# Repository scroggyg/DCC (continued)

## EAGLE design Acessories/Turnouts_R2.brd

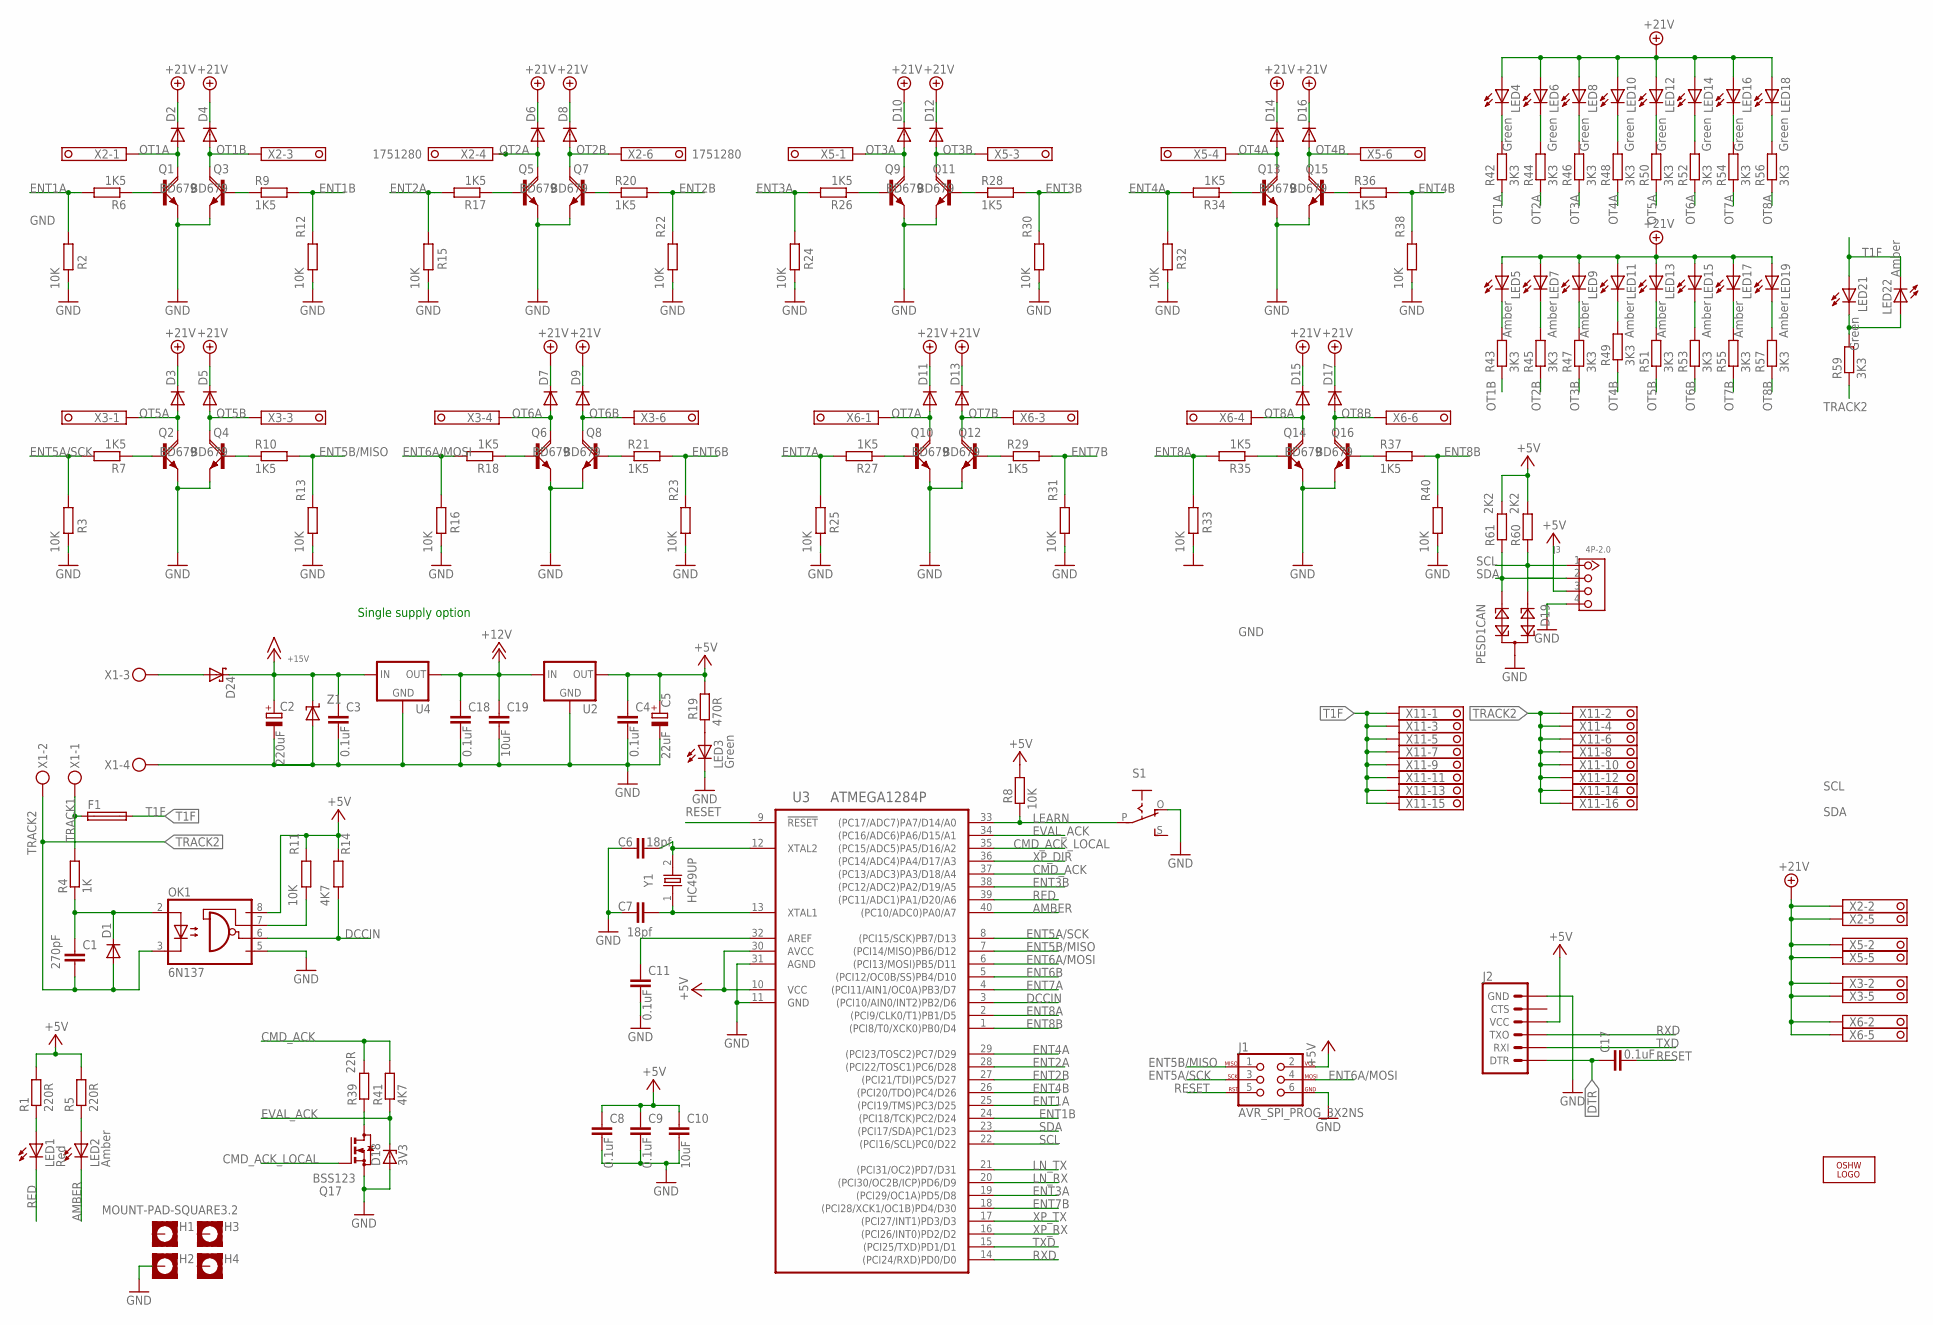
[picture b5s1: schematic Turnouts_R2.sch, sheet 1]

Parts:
C1: 270pF; C0805
C2: 220uF; E7,5-16
C3, C4, C8, C9, C11, C17, C18: 0.1uF; C0805
C5: 22uF; E2,5-5
C6, C7: 18pf; C0603
C10, C19: 10uF; C0805
D1, D2, D3, D4, D5, D6, D7, D8, D9, D10, D11, D12, D13, D14, D15, D16, D17: CGRM4002-G; SOD-123_MINI-SMA
D18: 3V3; SOT23
D19: PESD1CAN; SOT23
D24: MICROSMD-SCHOTTKY-DIODESMP; SMP
F1: TE5
H1, H2, H3, H4: MOUNT-PAD-SQUARE3.2; 3,2-PAD-SQUARE
J1: AVR_SPI_PROG_3X2NS; 2X3-NS
J2: 6_PIN_SERIAL_TARGET; 1X06
J3: 4P-2.0; HW4-2.0
LED1: Red; LED3MM
LED2, LED5, LED7, LED9, LED11, LED13, LED15, LED17, LED19, LED22: Amber; LED3MM
LED3, LED4, LED6, LED8, LED10, LED12, LED14, LED16, LED18, LED21: Green; LED3MM
LOGO1: OSHW_LOGO_6MILX0200-NT; OSHW_6X200_NOTEXT
OK1: 6N137; DIL08
Q1, Q2, Q3, Q4, Q5, Q6, Q7, Q8, Q9, Q10, Q11, Q12, Q13, Q14, Q15, Q16: BD679; TO126AV
Q17: BSS123; SOT23
R1, R5: 220R; R0805
R2, R3, R8, R11, R12, R13, R15, R16, R22, R23, R24, R25, R30, R31, R32, R33, R38, R40: 10K; R0805
R4: 1K; R0805
R6, R7, R9, R10, R17, R18, R20, R21, R26, R27, R28, R29, R34, R35, R36, R37: 1K5; R0805
R14, R41: 4K7; R0805
R19: 470R; R0805
R39: 22R; R0805
R42, R43, R44, R45, R46, R47, R48, R49, R50, R51, R52, R53, R54, R55, R56, R57, R59: 3K3; R0805
R60, R61: 2K2; R0805
S1: EG1218S; EG1218
U2, U4: V_REG_78XX-TO-220; TO-220-ALT
U3: ATMEGA1284P; DIP40
X1: MKDSN1,5/4-5,08
X2, X3, X5, X6: 1751280
X11: MKKDS1/8-3,5
Y1: HC49UP
Z1: TRANSZORB; SMB

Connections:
+5V: C4.1, C5.+, C8.1, C9.1, C10.1, J1.2, J2.4 (VCC), J3.3, OK1.8 (VCC), R1.2, R5.2, R8.2, R11.2, R14.2, R19.2, R60.2, R61.2, U2.OUT, U3.10 (VCC), U3.30 (AVCC); also elsewhere on the board
+12V: C18.1, C19.1, U2.IN, U4.OUT; also elsewhere on the board
+15V: C2.+, C3.1, D24.C, U4.IN, Z1.1 (C); also elsewhere on the board
+21V: D2.C, D3.C, D4.C, D5.C, D6.C, D7.C, D8.C, D9.C, D10.C, D11.C, D12.C, D13.C, D14.C, D15.C, D16.C, D17.C, LED4.A, LED5.A, LED6.A, LED7.A, LED8.A, LED9.A, LED10.A, LED11.A, LED12.A, LED13.A, LED14.A, LED15.A, LED16.A, LED17.A, LED18.A, LED19.A, X2.2, X2.5, X3.2, X3.5, X5.2, X5.5, X6.2, X6.5; also elsewhere on the board
AMBER: LED2.K (C), U3.40 ((PC10/ADC0)PA0/A7)
CMD_ACK: R39.2, R41.2, U3.37 ((PC13/ADC3)PA3/D18/A4); also elsewhere on the board
CMD_ACK_LOCAL: Q17.1 (G), U3.35 ((PC15/ADC5)PA5/D16/A2)
DCCIN: OK1.6 (VO), R14.1, U3.3 ((PCI10/AIN0/INT2)PB2/D6)
DTR: C17.1, J2.1 (DTR)
ENT1A: R2.2, R6.2, U3.25 ((PCI19/TMS)PC3/D25)
ENT1B: R9.2, R12.2, U3.24 ((PCI18/TCK)PC2/D24)
ENT2A: R15.2, R17.2, U3.28 ((PCI22/TOSC1)PC6/D28)
ENT2B: R20.2, R22.2, U3.27 ((PCI21/TDI)PC5/D27)
ENT3A: R24.2, R26.2, U3.19 ((PCI29/OC1A)PD5/D8)
ENT3B: R28.2, R30.2, U3.38 ((PC12/ADC2)PA2/D19/A5)
ENT4A: R32.2, R34.2, U3.29 ((PCI23/TOSC2)PC7/D29)
ENT4B: R36.2, R38.2, U3.26 ((PCI20/TDO)PC4/D26)
ENT5A/SCK: J1.3, R3.2, R7.2, U3.8 ((PCI15/SCK)PB7/D13)
ENT5B/MISO: J1.1, R10.2, R13.2, U3.7 ((PCI14/MISO)PB6/D12)
ENT6A/MOSI: J1.4, R16.2, R18.2, U3.6 ((PCI13/MOSI)PB5/D11)
ENT6B: R21.2, R23.2, U3.5 ((PCI12/OC0B/SS)PB4/D10)
ENT7A: R25.2, R27.2, U3.4 ((PCI11/AIN1/OC0A)PB3/D7)
ENT7B: R29.2, R31.2, U3.18 ((PCI28/XCK1/OC1B)PD4/D30)
ENT8A: R33.2, R35.2, U3.2 ((PCI9/CLK0/T1)PB1/D5)
ENT8B: R37.2, R40.2, U3.1 ((PCI8/T0/XCK0)PB0/D4)
EVAL_ACK: D18.3 (C), R41.1, U3.34 ((PC16/ADC6)PA6/D15/A1)
GND: C2.-, C3.2, C4.2, C5.-, C6.1, C7.1, C8.2, C9.2, C10.2, C11.2, C18.2, C19.2, D18.1 (A), D19.3, H2.B3,2, J1.6, J2.6 (GND), J3.4, LED3.K (C), OK1.5 (GND), Q1.E, Q2.E, Q3.E, Q4.E, Q5.E, Q6.E, Q7.E, Q8.E, Q9.E, Q10.E, Q11.E, Q12.E, Q13.E, Q14.E, Q15.E, Q16.E, Q17.2 (S), R2.1, R3.1, R12.1, R13.1, R15.1, R16.1, R22.1, R23.1, R24.1, R25.1, R30.1, R31.1, R32.1, R33.1, R38.1, R40.1, S1.O, U2.GND, U3.11 (GND), U3.31 (AGND), U4.GND, X1.4, Z1.2 (A); also elsewhere on the board
LEARN: R8.1, S1.P, U3.33 ((PC17/ADC7)PA7/D14/A0)
LN_RX: U3.20 ((PCI30/OC2B/ICP)PD6/D9); also elsewhere on the board
LN_TX: U3.21 ((PCI31/OC2)PD7/D31); also elsewhere on the board
unnamed: D24.A, X1.3
unnamed: C1.1, D1.C, OK1.2 (A), R4.1
unnamed: OK1.7 (VE), R11.1
unnamed: Q5.B, R17.1
unnamed: LED13.K (C), R51.2
unnamed: Q1.B, R6.1
unnamed: Q7.B, R20.1
unnamed: LED15.K (C), R53.2
unnamed: Q17.3 (D), R39.1
unnamed: Q9.B, R26.1
unnamed: LED17.K (C), R55.2
unnamed: LED19.K (C), R57.2
unnamed: LED5.K (C), R43.2
unnamed: LED7.K (C), R45.2
unnamed: LED9.K (C), R47.2
unnamed: LED11.K (C), R49.2
unnamed: LED4.K (C), R42.2
unnamed: LED6.K (C), R44.2
unnamed: LED8.K (C), R46.2
unnamed: LED10.K (C), R48.2
unnamed: LED12.K (C), R50.2
unnamed: LED14.K (C), R52.2
unnamed: LED16.K (C), R54.2
unnamed: LED18.K (C), R56.2
unnamed: LED21.K (C), LED22.A, R59.2
unnamed: Q11.B, R28.1
unnamed: Q13.B, R34.1
unnamed: Q15.B, R36.1
unnamed: Q2.B, R7.1
unnamed: Q3.B, R9.1
unnamed: Q4.B, R10.1
unnamed: LED3.A, R19.1
unnamed: LED1.A, R1.1
unnamed: LED2.A, R5.1
unnamed: Q6.B, R18.1
unnamed: Q8.B, R21.1
unnamed: Q10.B, R27.1
unnamed: Q12.B, R29.1
unnamed: Q14.B, R35.1
unnamed: Q16.B, R37.1
unnamed: C6.2, U3.12 (XTAL2), Y1.2
unnamed: C7.2, U3.13 (XTAL1), Y1.1
unnamed: C11.1, U3.32 (AREF)
OT1A: D2.A, Q1.C, R42.1, X2.1
OT1B: D4.A, Q3.C, R43.1, X2.3
OT2A: D6.A, Q5.C, R44.1, X2.4
OT2B: D8.A, Q7.C, R45.1, X2.6
OT3A: D10.A, Q9.C, R46.1, X5.1
OT3B: D12.A, Q11.C, R47.1, X5.3
OT4A: D14.A, Q13.C, R48.1, X5.4
OT4B: D16.A, Q15.C, R49.1, X5.6
OT5A: D3.A, Q2.C, R50.1, X3.1
OT5B: D5.A, Q4.C, R51.1, X3.3
OT6A: D7.A, Q6.C, R52.1, X3.4
OT6B: D9.A, Q8.C, R53.1, X3.6
OT7A: D11.A, Q10.C, R54.1, X6.1
OT7B: D13.A, Q12.C, R55.1, X6.3
OT8A: D15.A, Q14.C, R56.1, X6.4
OT8B: D17.A, Q16.C, R57.1, X6.6
RED: LED1.K (C), U3.39 ((PC11/ADC1)PA1/D20/A6)
RESET: C17.2, J1.5, U3.9 (!RESET); also elsewhere on the board
RXD: J2.3 (TXO), U3.14 ((PCI24/RXD)PD0/D0)
SCL: D19.1, J3.1, R60.1, U3.22 ((PCI16/SCL)PC0/D22); also elsewhere on the board
SDA: D19.2, J3.2, R61.1, U3.23 ((PCI17/SDA)PC1/D23); also elsewhere on the board
T1F: F1.2, LED21.A, LED22.K (C), X11.1, X11.3, X11.5, X11.7, X11.9, X11.11, X11.13, X11.15
TRACK1: F1.1, R4.2, X1.1
TRACK2: C1.2, D1.A, OK1.3 (C), R59.1, X1.2, X11.2, X11.4, X11.6, X11.8, X11.10, X11.12, X11.14, X11.16
TXD: J2.2 (RXI), U3.15 ((PCI25/TXD)PD1/D1)
XP_DIR: U3.36 ((PC14/ADC4)PA4/D17/A3); also elsewhere on the board
XP_RX: U3.16 ((PCI26/INT0)PD2/D2); also elsewhere on the board
XP_TX: U3.17 ((PCI27/INT1)PD3/D3); also elsewhere on the board

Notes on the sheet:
Single supply option

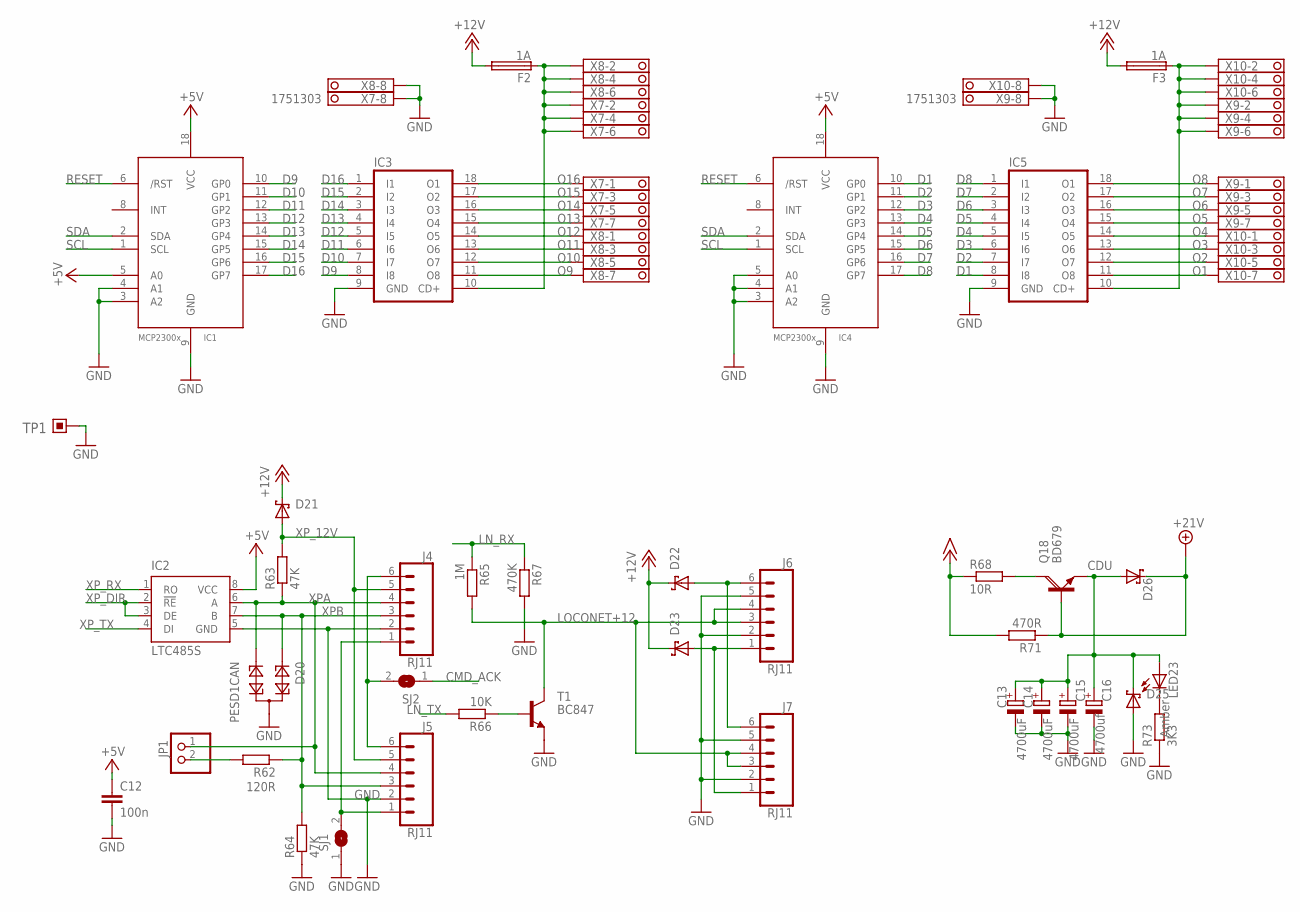
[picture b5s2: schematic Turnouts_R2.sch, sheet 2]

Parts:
C12: 100n; C0805
C13, C14, C15: 4700uF; E7,5-16
C16: 4700uf; E7,5-16
D20: PESD1CAN; SOT23
D21, D22, D23, D25, D26: MICROSMD-SCHOTTKY-DIODESMP; SMP
F2, F3: 1A; TE5
IC1, IC4: MCP23008/P; DIL18
IC2: LTC485S; SOIC8
IC3, IC5: ULN2803A; DIL18
J4, J5, J6, J7: RJ11; RJ11-6
JP1: PINHD-1X2; 1X02
LED23: Amber; LED3MM
Q18: BD679; TO126AV
R62: 120R; R0805
R63, R64: 47K; R0805
R65: 1M; R0805
R66: 10K; R0805
R67: 470K; R0805
R68: 10R; 0617/22
R71: 470R; 0411/12
R73: 3K3; R0805
SJ1, SJ2: SJ
T1: BC847; SOT23
TP1: TP1.5RUND; TP-1.5RUND
X7, X8, X9, X10: 1751303

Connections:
+5V: C12.1, IC1.5 (A0), IC1.18 (VCC), IC2.8 (VCC), IC4.18 (VCC); also elsewhere on the board
+12V: D21.C, D22.C, D23.C, F2.2, F3.2; also elsewhere on the board
+15V: R68.1, R71.2; also elsewhere on the board
+21V: D26.C, Q18.B, R71.1; also elsewhere on the board
CDU: C13.+, C14.+, C15.+, C16.+, D25.C, D26.A, LED23.A, Q18.E
CMD_ACK: SJ2.1; also elsewhere on the board
D1: IC4.10 (GP0), IC5.8 (I8)
D2: IC4.11 (GP1), IC5.7 (I7)
D3: IC4.12 (GP2), IC5.6 (I6)
D4: IC4.13 (GP3), IC5.5 (I5)
D5: IC4.14 (GP4), IC5.4 (I4)
D6: IC4.15 (GP5), IC5.3 (I3)
D7: IC4.16 (GP6), IC5.2 (I2)
D8: IC4.17 (GP7), IC5.1 (I1)
D9: IC1.10 (GP0), IC3.8 (I8)
D10: IC1.11 (GP1), IC3.7 (I7)
D11: IC1.12 (GP2), IC3.6 (I6)
D12: IC1.13 (GP3), IC3.5 (I5)
D13: IC1.14 (GP4), IC3.4 (I4)
D14: IC1.15 (GP5), IC3.3 (I3)
D15: IC1.16 (GP6), IC3.2 (I2)
D16: IC1.17 (GP7), IC3.1 (I1)
GND: C12.2, C13.-, C14.-, C15.-, C16.-, D20.3, D25.A, IC1.3 (A2), IC1.4 (A1), IC1.9 (GND), IC2.5 (GND), IC3.9 (GND), IC4.3 (A2), IC4.4 (A1), IC4.5 (A0), IC4.9 (GND), IC5.9 (GND), J4.2, J5.2, J6.2, J6.5, J7.2, J7.5, R64.1, R67.2, R73.1, SJ1.1, T1.2 (E), TP1.1, X7.8, X8.8, X9.8, X10.8; also elsewhere on the board
LN_RX: R65.1, R67.1; also elsewhere on the board
LN_TX: R66.2; also elsewhere on the board
LOCONET+12: J6.3, J6.4, J7.3, J7.4, R65.2, T1.3 (C)
unnamed: J4.1, J5.1, SJ1.2
unnamed: LED23.K (C), R73.2
unnamed: Q18.C, R68.2
unnamed: D23.A, J6.1, J7.1
unnamed: J4.6, J5.6, SJ2.2
unnamed: F2.1, IC3.10 (CD+), X7.2, X7.4, X7.6, X8.2, X8.4, X8.6
unnamed: JP1.2, R62.2
unnamed: F3.1, IC5.10 (CD+), X9.2, X9.4, X9.6, X10.2, X10.4, X10.6
unnamed: D22.A, J6.6, J7.6
unnamed: R66.1, T1.1 (B)
O1: IC5.11 (O8), X10.7
O2: IC5.12 (O7), X10.5
O3: IC5.13 (O6), X10.3
O4: IC5.14 (O5), X10.1
O5: IC5.15 (O4), X9.7
O6: IC5.16 (O3), X9.5
O7: IC5.17 (O2), X9.3
O8: IC5.18 (O1), X9.1
O9: IC3.11 (O8), X8.7
O10: IC3.12 (O7), X8.5
O11: IC3.13 (O6), X8.3
O12: IC3.14 (O5), X8.1
O13: IC3.15 (O4), X7.7
O14: IC3.16 (O3), X7.5
O15: IC3.17 (O2), X7.3
O16: IC3.18 (O1), X7.1
RESET: IC1.6 (/RST), IC4.6 (/RST); also elsewhere on the board
SCL: IC1.1 (SCL), IC4.1 (SCL); also elsewhere on the board
SDA: IC1.2 (SDA), IC4.2 (SDA); also elsewhere on the board
XPA: D20.2, IC2.6 (A), J4.4, J5.4, JP1.1, R63.1
XPB: D20.1, IC2.7 (B), J4.3, J5.3, R62.1, R64.2
XP_12V: D21.A, J4.5, J5.5, R63.2
XP_DIR: IC2.2 (!RE), IC2.3 (DE); also elsewhere on the board
XP_RX: IC2.1 (RO); also elsewhere on the board
XP_TX: IC2.4 (DI); also elsewhere on the board

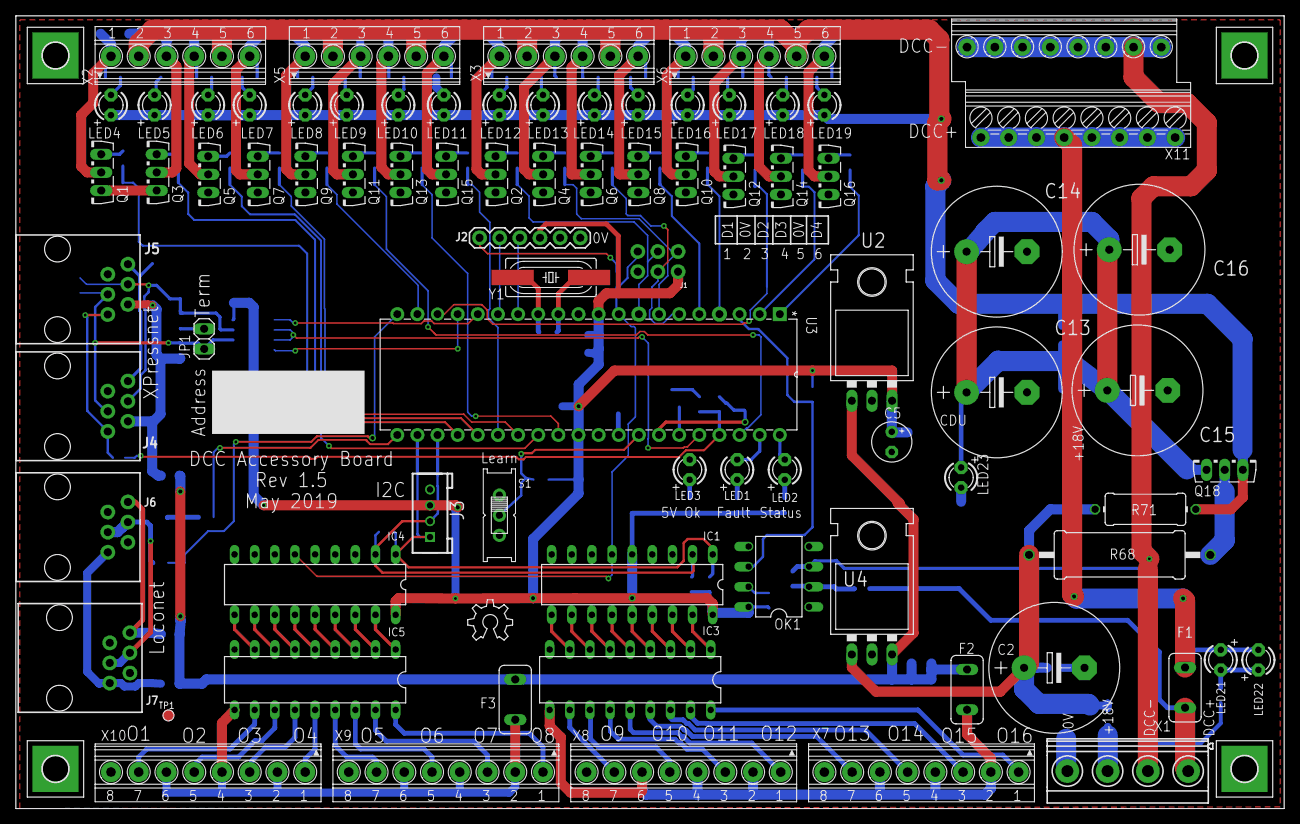
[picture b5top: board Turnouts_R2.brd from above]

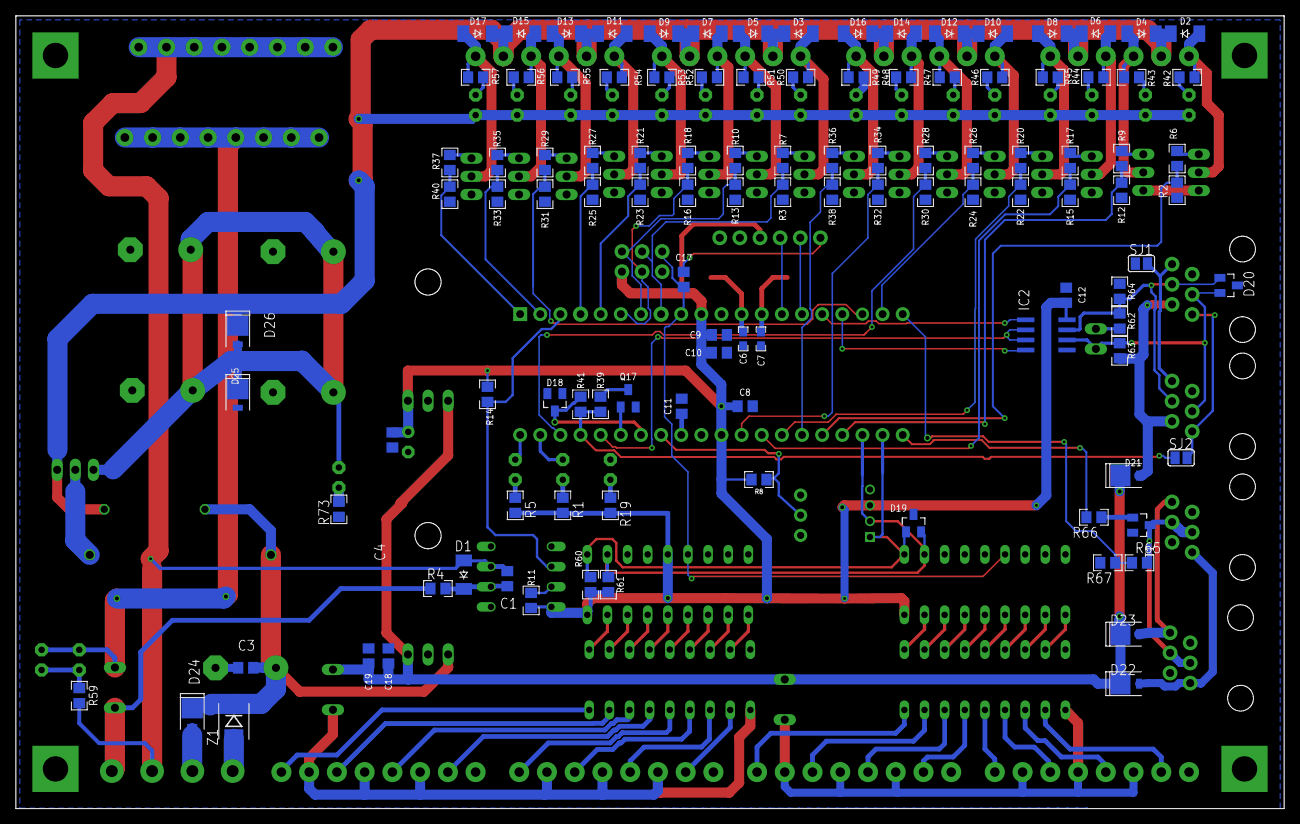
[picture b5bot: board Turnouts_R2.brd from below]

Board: 2 copper layers, 160.0 x 100.0 mm, 196 parts (112 on the bottom side), 148 nets.

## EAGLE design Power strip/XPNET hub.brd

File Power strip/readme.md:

PCB files for 2 power distribution strips
Supports building a layout for exhibition inmodules
Each module interconnectes with 4 wires
DCC - 2
+18V & 0V
Could work with 16V AC, but LEDs not tested as such

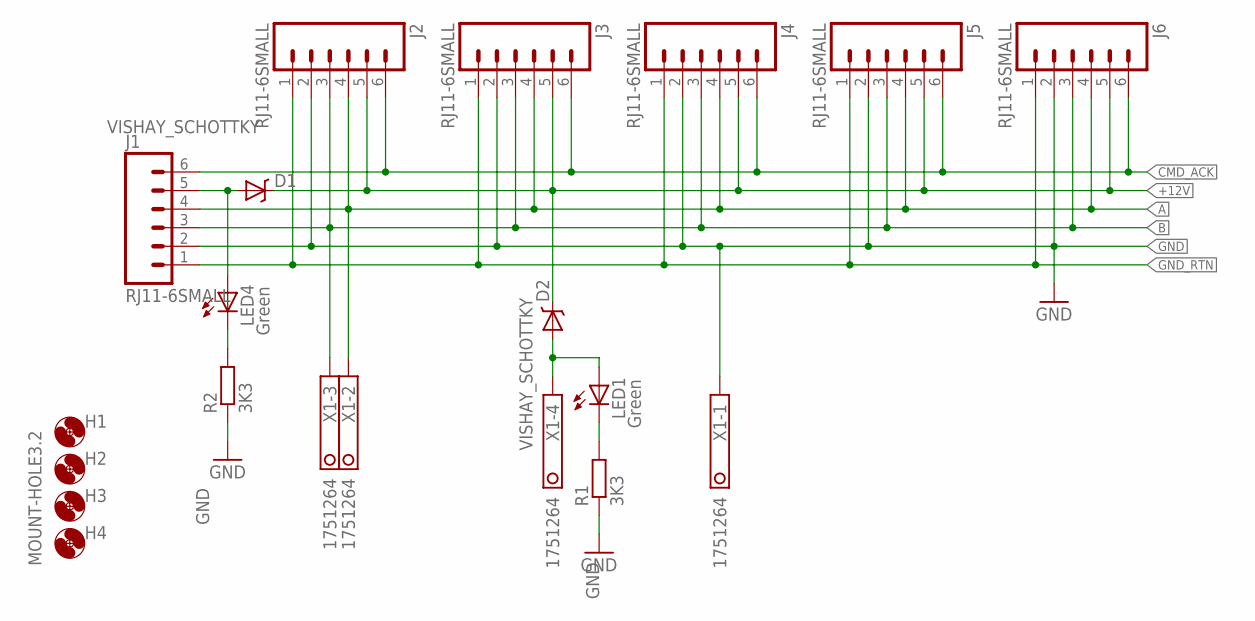
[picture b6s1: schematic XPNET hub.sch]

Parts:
D1, D2: VISHAY_SCHOTTKY; DO-220AA
H1, H2, H3, H4: MOUNT-HOLE3.2; 3,2
J1, J2, J3, J4, J5, J6: RJ11-6SMALL; RJ11-6-2
LED1, LED4: Green; LED3MM
R1, R2: 3K3; R0805
X1: 1751264

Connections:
+12V: D1.CATHODE (C), D2.CATHODE (C), J2.5, J3.5, J4.5, J5.5, J6.5
+21V1: D2.ANODE (A), LED1.A, X1.4
A: J1.4, J2.4, J3.4, J4.4, J5.4, J6.4, X1.2
B: J1.3, J2.3, J3.3, J4.3, J5.3, J6.3, X1.3
CMD_ACK: J1.6, J2.6, J3.6, J4.6, J5.6, J6.6
GND: J1.2, J2.2, J3.2, J4.2, J5.2, J6.2, R1.1, R2.1, X1.1
GND_RTN: J1.1, J2.1, J3.1, J4.1, J5.1, J6.1
unnamed: D1.ANODE (A), J1.5, LED4.A
unnamed: LED1.K (C), R1.2
unnamed: LED4.K (C), R2.2

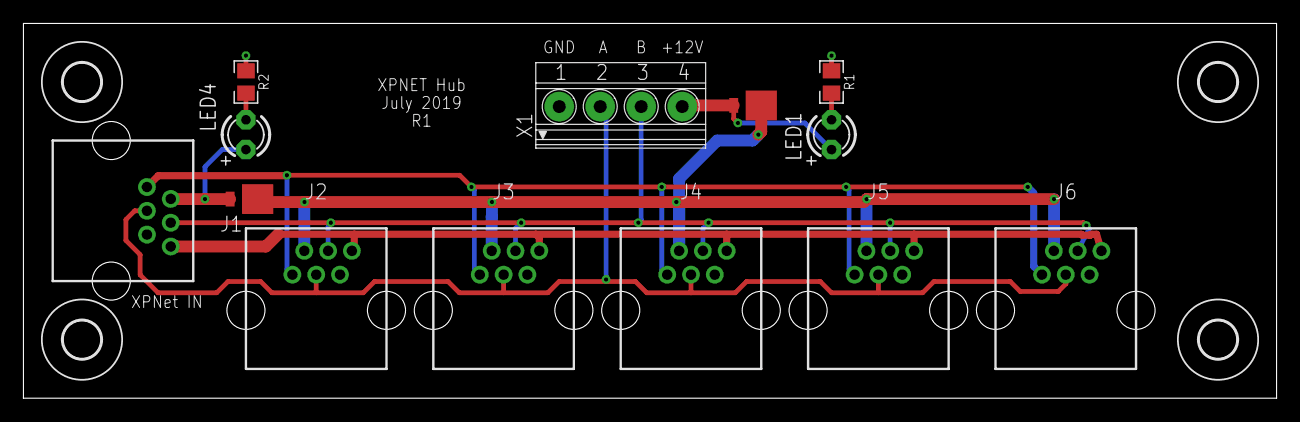
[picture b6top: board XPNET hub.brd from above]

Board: 2 copper layers, 107.0 x 32.0 mm, 17 parts (0 on the bottom side), 10 nets.

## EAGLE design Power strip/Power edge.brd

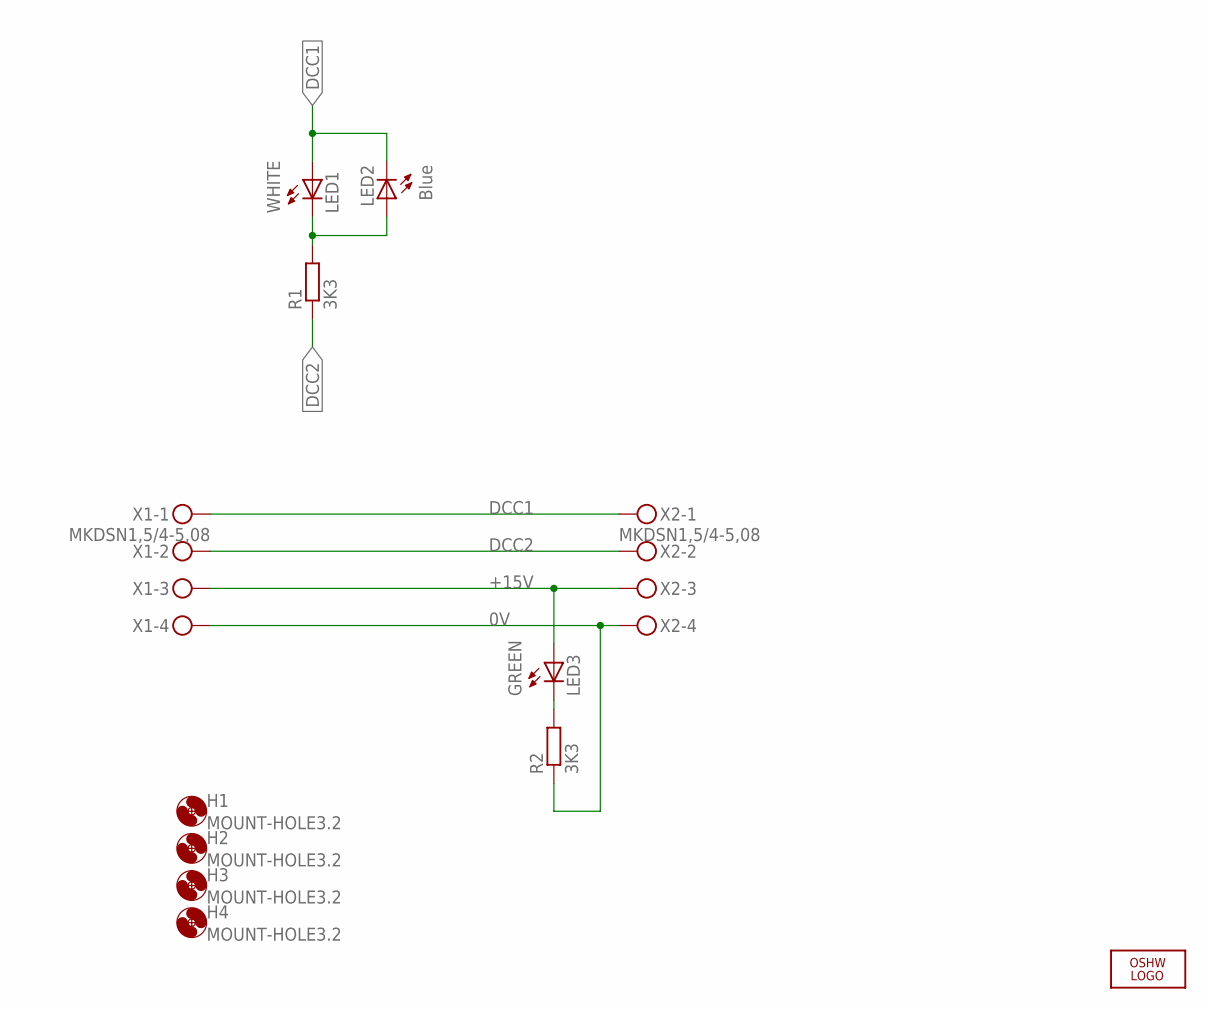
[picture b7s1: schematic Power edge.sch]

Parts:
H1, H2, H3, H4: MOUNT-HOLE3.2; 3,2
LED1: WHITE; LED3MM
LED2: Blue; LED3MM
LED3: GREEN; LED3MM
LOGO1: OSHW_LOGO_6MILX0200-NT; OSHW_6X200_NOTEXT
R1, R2: 3K3; R0805
X1, X2: MKDSN1,5/4-5,08

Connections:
0V: R2.1, X1.4, X2.4
+15V: LED3.A, X1.3, X2.3
DCC1: LED1.A, LED2.K (C), X1.1, X2.1
DCC2: R1.1, X1.2, X2.2
unnamed: LED3.K (C), R2.2
unnamed: LED1.K (C), LED2.A, R1.2

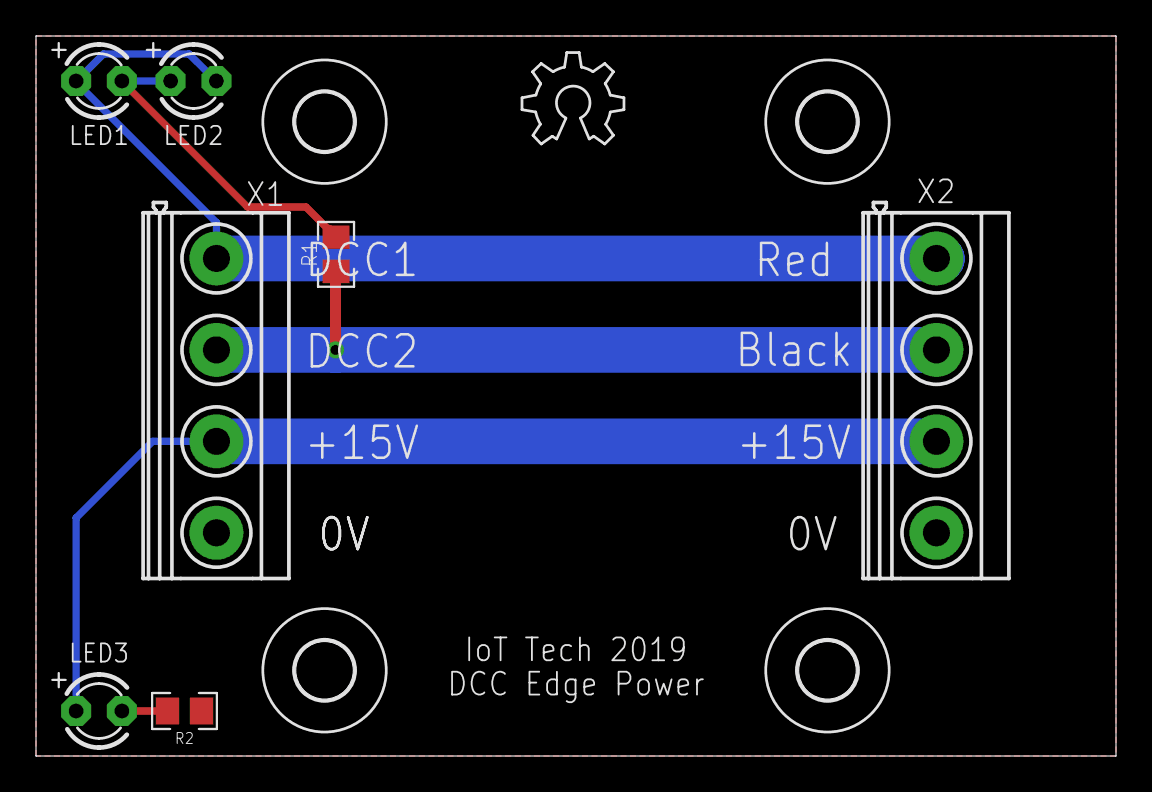
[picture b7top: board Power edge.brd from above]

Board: 2 copper layers, 60.0 x 40.0 mm, 12 parts (0 on the bottom side), 6 nets.

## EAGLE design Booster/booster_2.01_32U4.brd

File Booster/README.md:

Booster based on design by Wolfgang Kufer

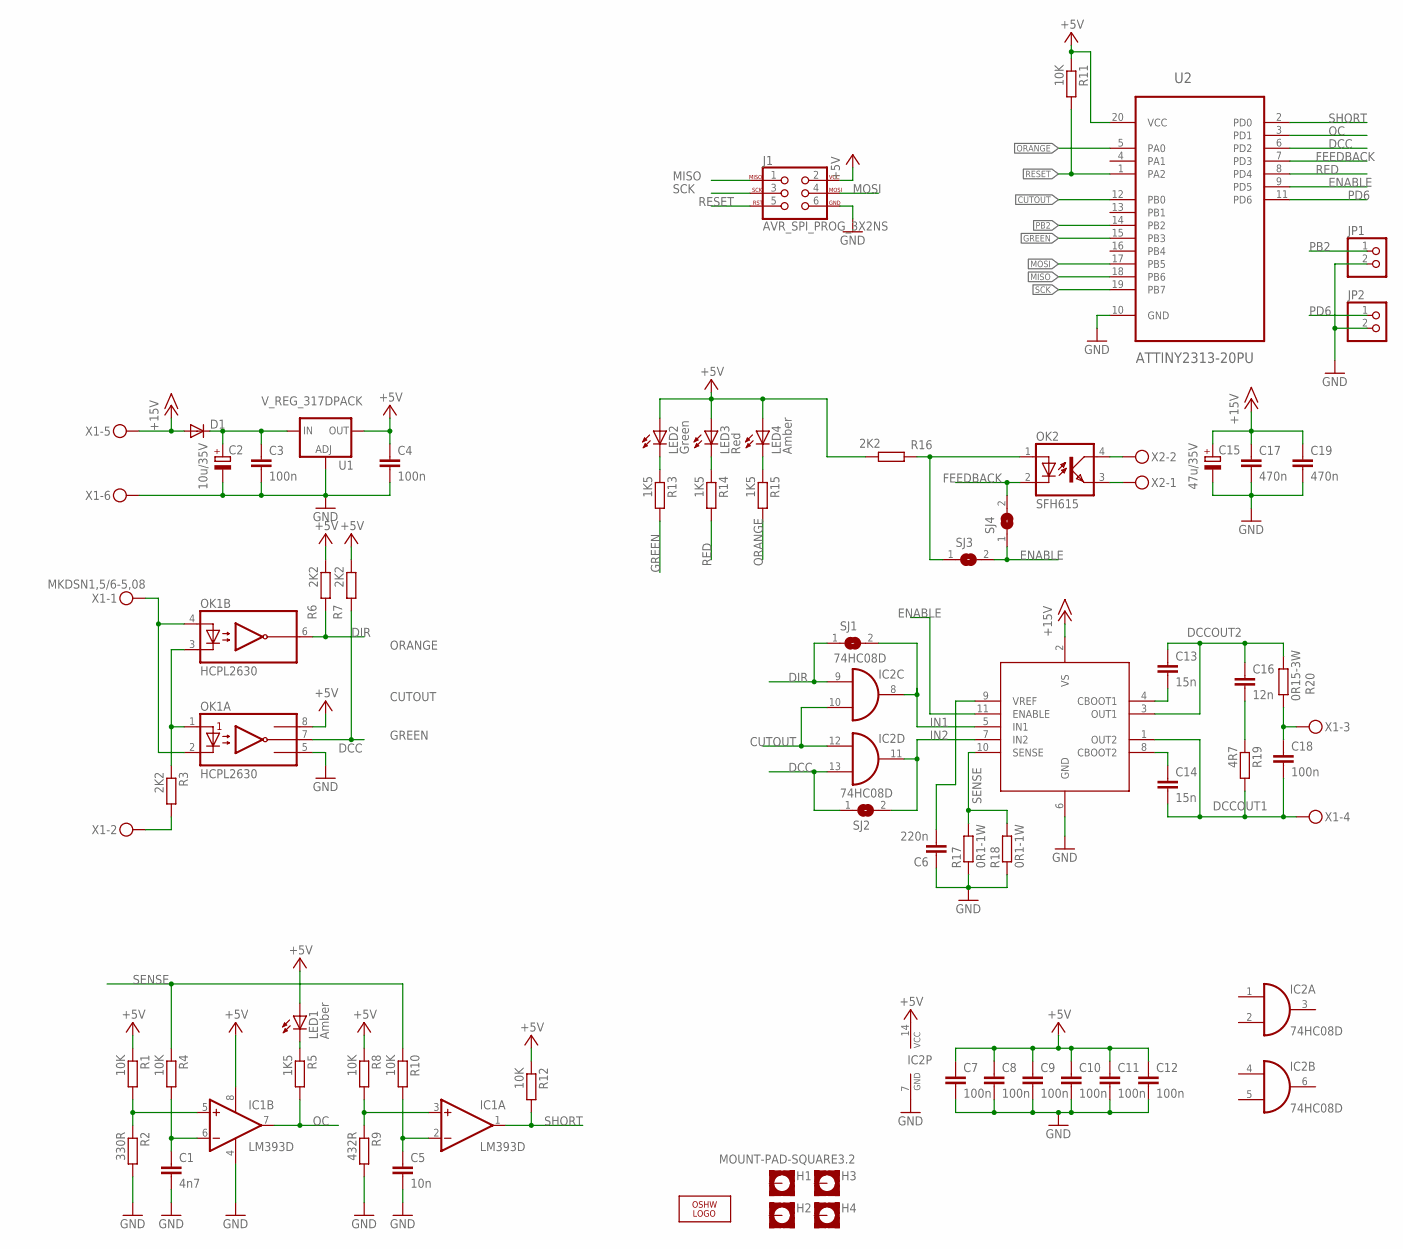
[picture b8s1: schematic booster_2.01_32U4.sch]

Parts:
C1: 4n7; C0805
C2: 10u/35V; E2,5-5
C3, C4, C7, C8, C9, C10, C11, C12, C18: 100n; C0805
C5: 10n; C0805
C6: 220n; C0805
C13, C14: 15n; C0805
C15: 47u/35V; E2,5-5
C16: 12n; C0805
C17, C19: 470n; C1812
D1: DIODE-SMB; SMB
H1, H2, H3, H4: MOUNT-PAD-SQUARE3.2; 3,2-PAD-SQUARE
IC1: LM393D; SO08
IC2: 74HC08D; SO14
J1: AVR_SPI_PROG_3X2NS; 2X3-NS
JP1, JP2: PINHD-1X2; 1X02
LED1, LED4: Amber; LED3MM
LED2: Green; LED3MM
LED3: Red; LED3MM
LOGO1: OSHW_LOGO_6MILX0200-NT; OSHW_6X200_NOTEXT
OK1: HCPL2630; DIL08
OK2: SFH615; DIL04
R1, R4, R8, R10, R11, R12: 10K; R0805
R2: 330R; R0805
R3, R6, R7, R16: 2K2; R0805
R5, R13, R14, R15: 1K5; R0805
R9: 432R; R0805
R17, R18: 0R1-1W; R2512
R19: 4R7; R0805
R20: 0R15-3W; P0817V
SJ1, SJ2, SJ3, SJ4: SJ
U1: V_REG_317DPACK; V-REG_DPACK
U2: ATTINY2313-20PU; DIP254P762X533-20
U3: L6203; ZIP_11
X1: MKDSN1,5/6-5,08
X2: MKDSN1,5/2-5,08

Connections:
+5V: C4.1, C7.1, C8.1, C9.1, C10.1, C11.1, C12.1, IC1.8 (V+), IC2.14 (VCC), J1.2, LED1.A, LED2.A, LED3.A, LED4.A, OK1.8 (VCC), R1.1, R6.1, R7.1, R8.1, R11.1, R12.1, R16.1, U1.4 (OUT), U2.20 (VCC)
+15V: C15.+, C17.1, C19.1, D1.A, U3.2 (VS), X1.5
CUTOUT: IC2.10 (I1), IC2.12 (I0), U2.12 (PB0)
DCC: IC2.13 (I1), OK1.7 (VO1), R7.2, SJ2.1, U2.6 (PD2)
DCCOUT1: C14.2, C18.2, R19.2, U3.1 (OUT2), X1.4
DCCOUT2: C13.1, C16.1, R20.2, U3.3 (OUT1)
DIR: IC2.9 (I0), OK1.6 (VO2), R6.2, SJ1.1
ENABLE: SJ3.2, SJ4.1, U2.9 (PD5), U3.11 (ENABLE)
FEEDBACK: OK2.2 (C), SJ4.2, U2.7 (PD3)
GND: C1.2, C2.-, C3.2, C4.2, C5.2, C6.1, C7.2, C8.2, C9.2, C10.2, C11.2, C12.2, C15.-, C17.2, C19.2, IC1.4 (V-), IC2.7 (GND), J1.6, JP1.2, JP2.2, OK1.5 (GND), R2.2, R9.2, R17.1, R18.1, U1.1 (ADJ), U2.10 (GND), U3.6 (GND), X1.6
GREEN: R13.2, U2.15 (PB3)
IN1: IC2.8 (O), SJ1.2, U3.5 (IN1)
IN2: IC2.11 (O), SJ2.2, U3.7 (IN2)
MISO: J1.1, U2.18 (PB6)
MOSI: J1.4, U2.17 (PB5)
unnamed: OK1.1 (A1), OK1.3 (C2), R3.1
unnamed: OK1.2 (C1), OK1.4 (A2), X1.1
unnamed: R3.2, X1.2
unnamed: IC1.5 (+IN), R1.2, R2.1
unnamed: C1.1, IC1.6 (-IN), R4.2
unnamed: OK2.4 (COL), X2.2
unnamed: IC1.3 (+IN), R8.2, R9.1
unnamed: C5.1, IC1.2 (-IN), R10.2
unnamed: OK2.3 (EMIT), X2.1
unnamed: LED1.K (C), R5.1
unnamed: C2.+, C3.1, D1.C, U1.3 (IN)
unnamed: LED2.K (C), R13.1
unnamed: C18.1, R20.1, X1.3
unnamed: OK2.1 (A), R16.2, SJ3.1
unnamed: LED3.K (C), R14.1
unnamed: LED4.K (C), R15.1
unnamed: C6.2, U3.9 (VREF)
unnamed: C16.2, R19.1
unnamed: C13.2, U3.4 (CBOOT1)
unnamed: C14.1, U3.8 (CBOOT2)
OC: IC1.7 (OUT), R5.2, U2.3 (PD1)
ORANGE: R15.2, U2.5 (PA0)
PB2: JP1.1, U2.14 (PB2)
PD6: JP2.1, U2.11 (PD6)
RED: R14.2, U2.8 (PD4)
RESET: J1.5, R11.2, U2.1 (PA2)
SCK: J1.3, U2.19 (PB7)
SENSE: R4.1, R10.1, R17.2, R18.2, U3.10 (SENSE)
SHORT: IC1.1 (OUT), R12.2, U2.2 (PD0)

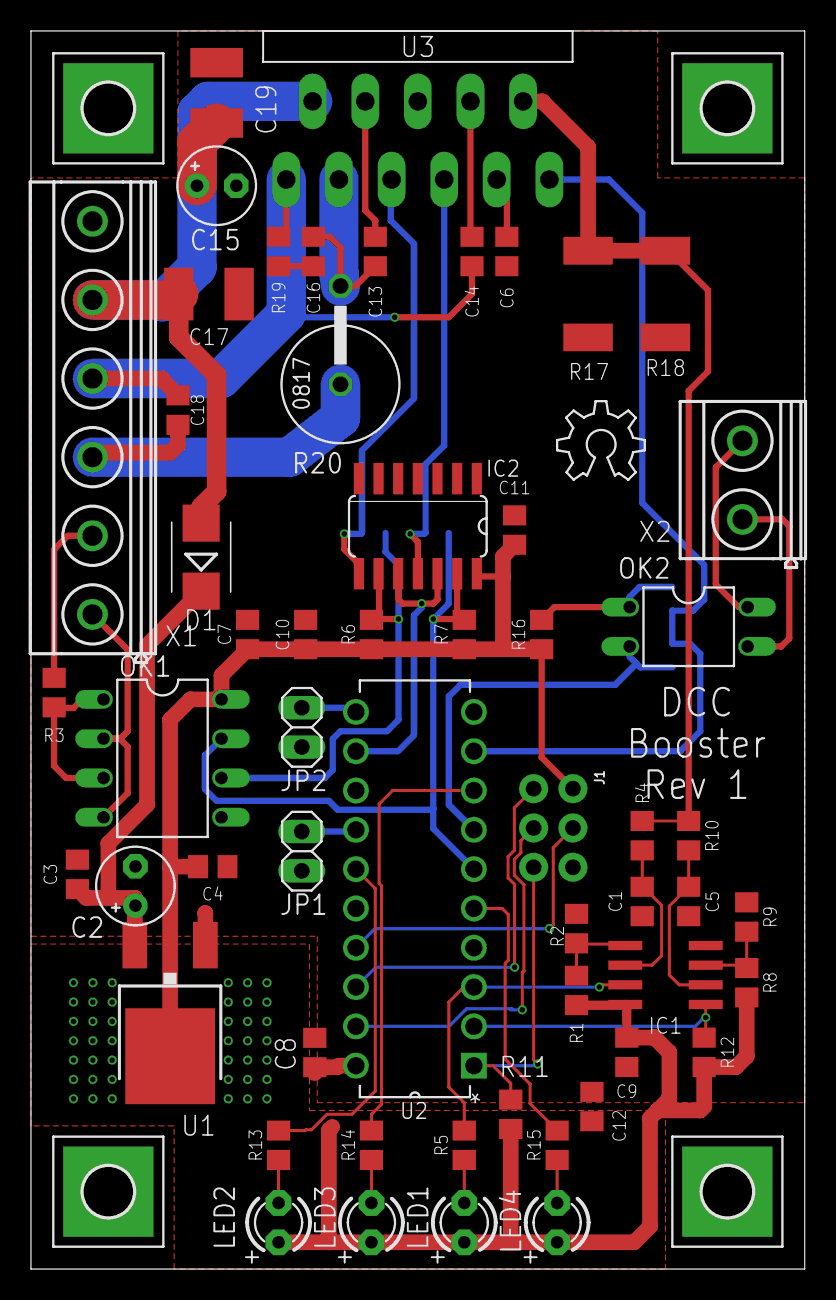
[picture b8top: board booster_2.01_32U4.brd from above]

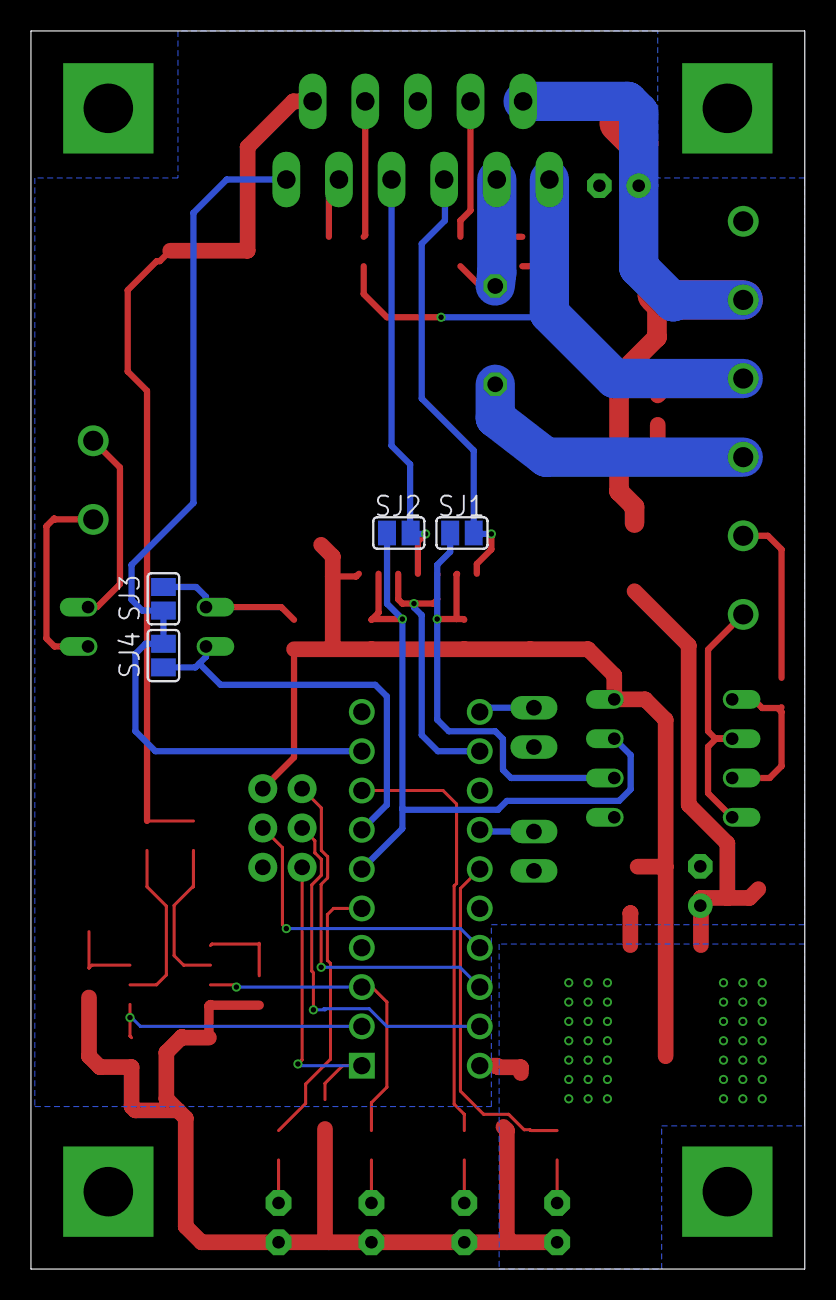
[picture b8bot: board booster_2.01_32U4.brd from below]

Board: 2 copper layers, 50.0 x 80.0 mm, 65 parts (4 on the bottom side), 44 nets.

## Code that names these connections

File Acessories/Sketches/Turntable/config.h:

 /*
 * Bobuino DCC Configuration file for 1284P
 * Copyright Lumenid Limited 2018
 */
 /*
 * EEPROM Memory map
 */
 #define ROCO             // Used to indicate that system is connected to Roco 
#define ver_add           2
#define ser_add           ver_add+2
#define ADDRESS_LSB       ser_add+2   
#define ADDRESS_MSB       ADDRESS_LSB+1
#define PULSE_TIME        ADDRESS_MSB+2
#define RECHARGE_TIME     PULSE_TIME+1
#define ACTIVE_STATE      RECHARGE_TIME+1
#define debug_add         ACTIVE_STATE+1 
/* Outputs and inputs */             
#define ENT1A 25
#define ENT1B 24
#define ENT2A 28
#define ENT2B 27
#define ENT3A 8
#define ENT3B 19
#define ENT4A 29
#define ENT4B 26
#define ENT5A 13
#define ENT5B 12
#define ENT6A 11
#define ENT6B 10
#define ENT7A 7
#define ENT7B 30
#define ENT8A 5
#define ENT8B 4
#define XP_DIR 17
#define red     20         // Fault LED
#define amber   21          // Status LED
#define LEARNINGBUTTON A0          // Learn input


// I2C defines
#define PCA9557 0x18          // I2C address
#define  PCA9557_INP_PORT_REG    0x00  // input port
/**
 * Output port is read/write, writing to input bits has no effect.
 * This internal reg outputs are qualified by the config pin dir register
 * Reading this reg returns the value of this internal register, NOT
 * the actual device pin. So reading this only confirms its setting.
 * Read the input port to read the actual value on all device I/O pins.
 */
#define PCA9557_OUT_PORT_REG    0x01  // output port
/**
 * Polarity inversion register is read/write.
 * invert polarity of input port if bit is 1
 * POR=0xF0
 */
#define PCA9557_INP_INVERT_REG  0x02
/**
 * Config register sets each bit's mode: 1=input, 0=output
 * POR = 0xFF (all I/O bits are inputs)
 */
 #define PCA9557_CONFIG_REG  0x03
#define maxleds     3
#define maxturnouts 8
